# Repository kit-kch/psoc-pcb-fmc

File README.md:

# PSoC FMC Extension PCB

This repository contains schematic, layout and BOM for the PSoC FMC extension PCB.
The PCB provides all peripherals that are used to realize the [PSoC Audio Player](https://kch.dev/psoc).
It is primarily meant to be used with the Zedboard for FPGA prototyping, but it can also serve as a test board for the PSoC ASIC.

The following features are provided by the PCB:
* 98.304 MHz oscillator ([XLH53V098.304000X](doc/REN_XL_Crystal_Oscillators_Datasheet_DST_20220302-1954959-1.pdf)) for SoC clock
* 64 MBit QSPI Flash ([W25Q64JVSSIM](doc/w25q64jv_dtr_revj_03272018_plus-1489809.pdf))
* USB/UART bridge ([CP2102N](doc/cp2102n_datasheet-1634912.pdf))
* 3 LEDs
* 2 [push buttons](doc/EVPBF.pdf)
* [5-way digital joystick](doc/SKRHAAE010.pdf)
* 128x32 [OLED display](https://www.waveshare.com/0.91inch-oled-module.htm) (I2C)
* I2S DAC with output filter networks ([CS4344-CZZR](doc/CS4344-45-48_F2.pdf))
* [3.5mm audio jack](doc/sj_352x_smt-1779397.pdf) for I2S DAC
* [3.5mm audio jack](doc/sj_352x_smt-1779397.pdf) directly connected to FMC
* [MicroSD card connector](doc/MOLEX_472192001_sd.pdf) (1-bit data line only)
* Power switch network: Power PCB from FMC 12V, power connector or UART usb connector
* 5V power regulator ([AP62300WU](doc/AP62300_AP62301_AP62300T.pdf))
* 3.3V power regulator (AMS1117-3.3)
* 1.8V power regulator (LM1117MPX-ADJ)
* Power indicator LEDs
* [USB-C connector](doc/usb4110.pdf) for UART
* [USB-C connector](doc/usb4110.pdf) for power
* [FMC LPC connector](doc/asp-134604-01-mkt-1546032.pdf) to connect to FPGA or ASIC
* 2 [40-pin pin headers](doc/SBH11-NBPC.pdf) for debugging of any signal
* Connector for future extensions (based on KiCAD RFM69HW footprint)
* Arduino-like connector for future extensions

For more details, see the [schematic](psoc.pdf):

## Ordering the PCBs

PCBs were ordered from [aisler.net](https://aisler.net) using the [fab.zip](fab.zip) file.
Make sure to use a stencil with 150µm thickness for proper FMC connector soldering.

## More Information and Documentation

* Project Website and Documentation: [kch.dev/psoc](https://kch.dev/psoc)
* Project Schematic: [psoc.pdf](psoc.pdf)

Additional documentation:
* [FMC Documentation](https://fmchub.github.io/appendix/VITA57_FMC_HPC_LPC_SIGNALS_AND_PINOUT.html)
* [USB-C Termination](https://community.cypress.com/t5/Knowledge-Base-Articles/Termination-Resistors-Required-for-the-USB-Type-C-Connector/ta-p/253544)
* [Audio TRS Standard](https://components101.com/connectors/35mm-audio-jack)

## Note and Limitations

### JTAG

* The board unfortunately does not provide convenient access to JTAG pins, although the debug header can be used.
  As a workaround, [psoc-pcb-jtag](https://github.com/kit-kch/psoc-pcb-jtag) can be connected to the USB header.

### Powering the IHP ASIC

The [IHP SG13G2 ASIC](https://github.com/IHP-GmbH/TO_Sep2025/pull/4) requires an 1.2V source instead of the 1.8V on this board.
Although the regulator on the board is adjustable, it can't go down to 1.2V.

As a simple solution, some parts can be replaced to provide 1.2V output:
* `U7` with `TLV76112DCYR` 1A 1.2V regulator
* `R51` with 0 Ohm (short)
* Remove `R50`
* Remove `C26`

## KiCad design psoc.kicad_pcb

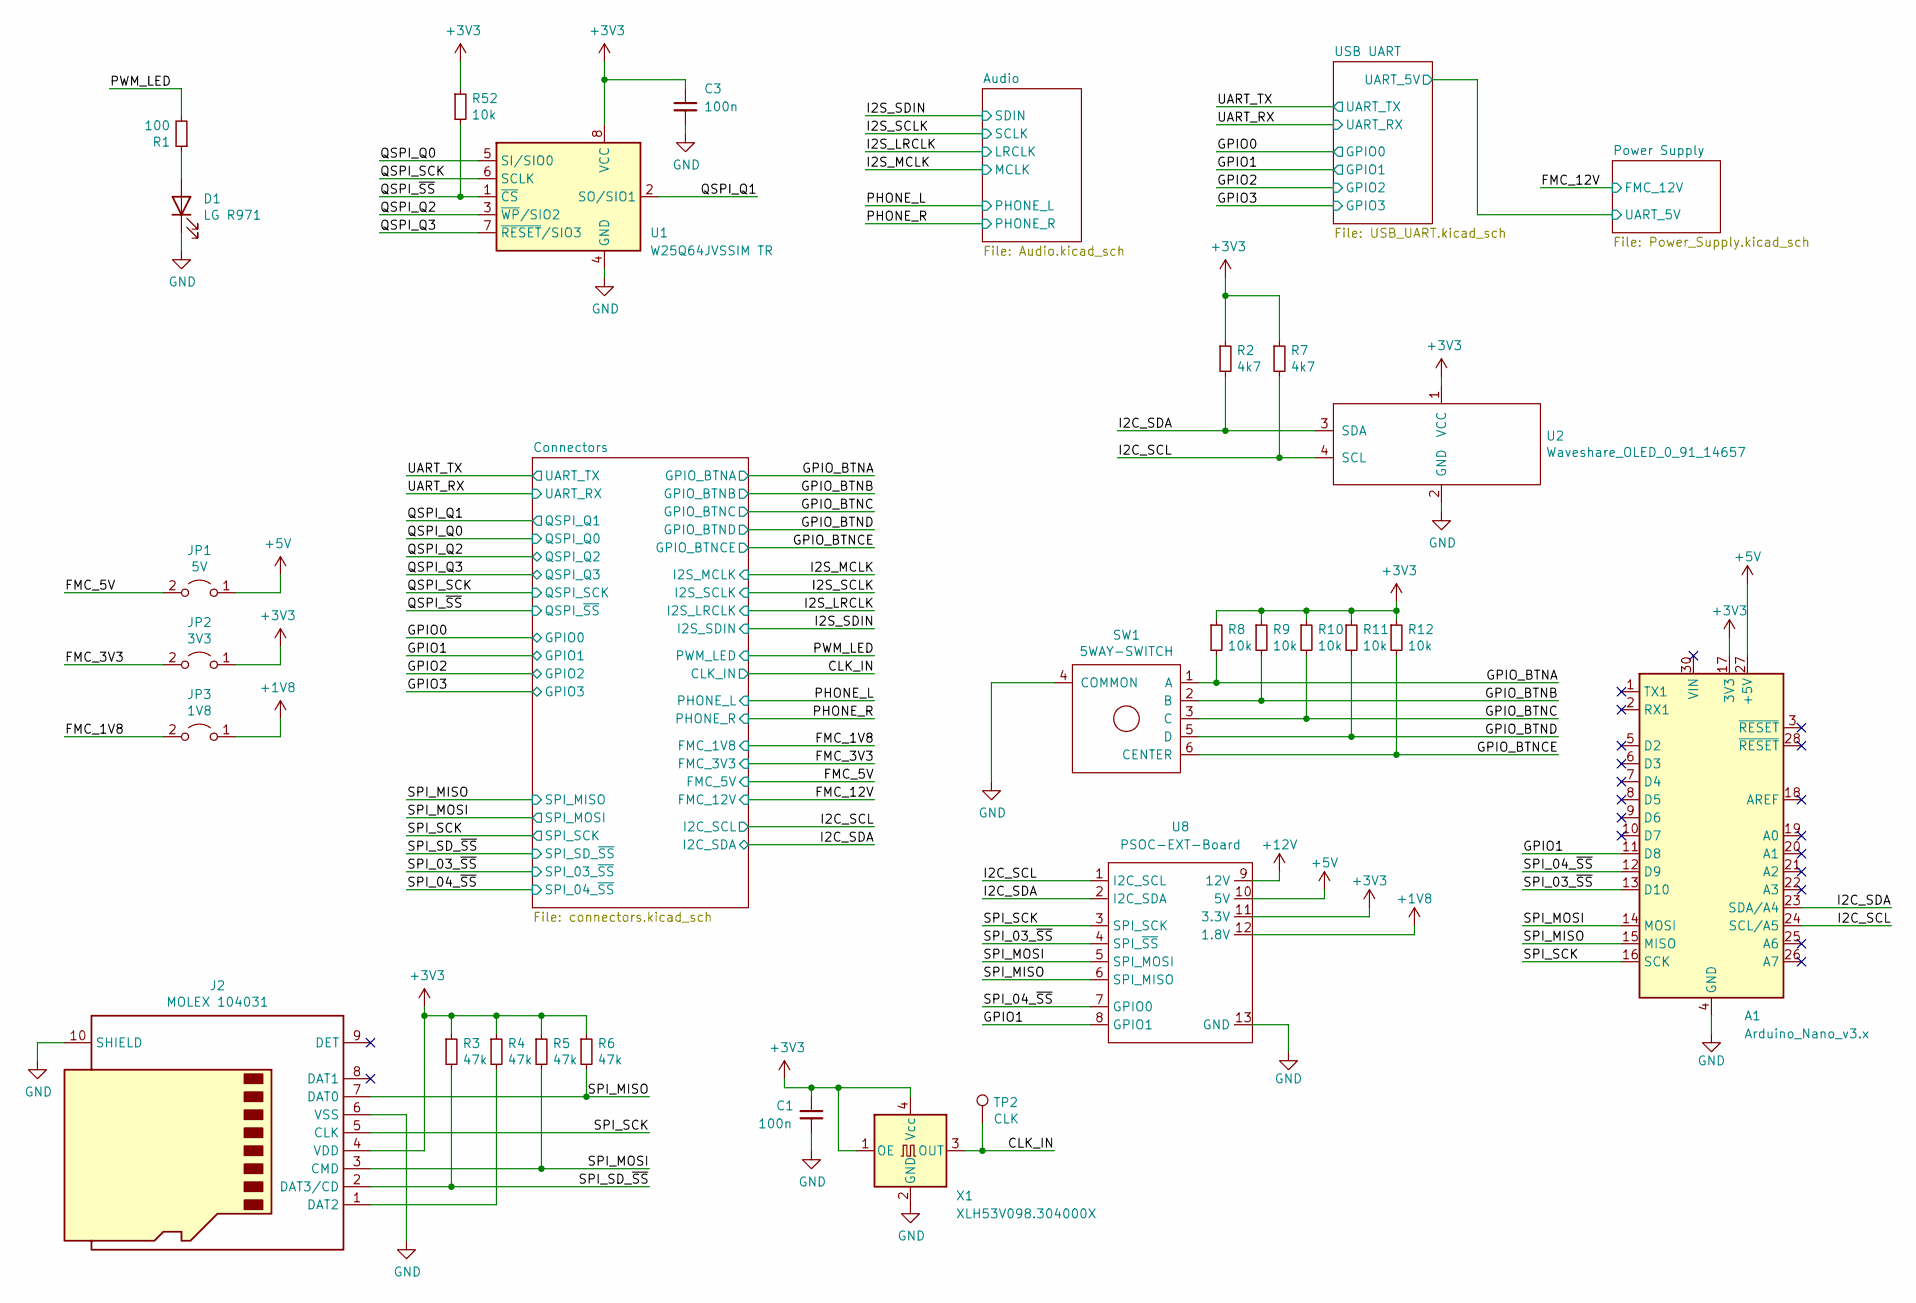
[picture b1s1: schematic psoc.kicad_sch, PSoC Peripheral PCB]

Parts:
A1: Arduino_Nano_v3.x; Arduino_Nano
C1, C3: 100n; C_0805_2012Metric; MPN 100nF 0805
D1: LG R971; LED_0805_2012Metric; MPN LG R971-KN-1
J2: MOLEX 104031; microSD_HC_Molex_104031-0811; MPN 1040310811
JP1: 5V; PinHeader_1x02_P2.54mm_Vertical; MPN 2302-6111TG
JP2: 3V3; PinHeader_1x02_P2.54mm_Vertical; MPN 2302-6111TG
JP3: 1V8; PinHeader_1x02_P2.54mm_Vertical; MPN 2302-6111TG
R1: 100; R_0805_2012Metric; MPN 0805 100
R2, R7: 4k7; R_0805_2012Metric; MPN 4k7 0805
R3, R4, R5, R6: 47k; R_0805_2012Metric; MPN 47k 0805
R8, R9, R10, R11, R12, R52: 10k; R_0805_2012Metric; MPN 10k 0805
SW1: 5WAY-SWITCH; SKRHAAE010; MPN SKRHAAE010
TP2: CLK; TestPoint_Pad_1.0x1.0mm
U1: W25Q64JVSSIM TR; SOIC-8_5.3x5.3mm_P1.27mm; MPN W25Q64JVSSIM TR
U2: Waveshare_OLED_0_91_14657; Waveshare_OLED_091
U8: PSOC-EXT-Board; PSOC_EXT_BOARD
X1: XLH53V098.304000X; Oscillator_SMD_Renesas_LGA-6_5x3.2mm_P1.25mm; MPN XLH53V098.304000X

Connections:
+1V8: JP3.1 (A), U8.12 (1.8V); also elsewhere on the board
+3V3: A1.17 (3V3), C1.1, C3.1, J2.4 (VDD), JP2.1 (A), R2.1, R3.1, R4.1, R5.1, R6.1, R7.1, R8.1, R9.1, R10.1, R11.1, R12.1, R52.1, U1.8 (VCC), U2.1 (VCC), U8.11 (3.3V), X1.1 (OE), X1.4 (Vcc); also elsewhere on the board
+5V: A1.27 (+5V), JP1.1 (A), U8.10 (5V); also elsewhere on the board
+12V: U8.9 (12V); also elsewhere on the board
/CLK_IN: TP2.1, X1.3 (OUT); also elsewhere on the board
/FMC_1V8: JP3.2 (B); also elsewhere on the board
/FMC_3V3: JP2.2 (B); also elsewhere on the board
/FMC_5V: JP1.2 (B); also elsewhere on the board
/GPIO1: A1.11 (D8), U8.8 (GPIO1); also elsewhere on the board
/GPIO_BTNA: R8.2, SW1.1 (A); also elsewhere on the board
/GPIO_BTNB: R9.2, SW1.2 (B); also elsewhere on the board
/GPIO_BTNC: R10.2, SW1.3 (C); also elsewhere on the board
/GPIO_BTNCE: R12.2, SW1.6 (CENTER); also elsewhere on the board
/GPIO_BTND: R11.2, SW1.5 (D); also elsewhere on the board
/I2C_SCL: A1.24 (SCL/A5), R7.2, U2.4 (SCL), U8.1 (I2C_SCL); also elsewhere on the board
/I2C_SDA: A1.23 (SDA/A4), R2.2, U2.3 (SDA), U8.2 (I2C_SDA); also elsewhere on the board
/PWM_LED: R1.2; also elsewhere on the board
/QSPI_Q0: U1.5 (SI/SIO0); also elsewhere on the board
/QSPI_Q1: U1.2 (SO/SIO1); also elsewhere on the board
/QSPI_Q2: U1.3 (~WP/SIO2); also elsewhere on the board
/QSPI_Q3: U1.7 (~RESET/SIO3); also elsewhere on the board
/QSPI_SCK: U1.6 (SCLK); also elsewhere on the board
/QSPI_~SS: R52.2, U1.1 (~CS); also elsewhere on the board
/SPI_03_~SS: A1.13 (D10), U8.4 (SPI_~SS); also elsewhere on the board
/SPI_04_~SS: A1.12 (D9), U8.7 (GPIO0); also elsewhere on the board
/SPI_MISO: A1.15 (MISO), J2.7 (DAT0), R6.2, U8.6 (SPI_MISO); also elsewhere on the board
/SPI_MOSI: A1.14 (MOSI), J2.3 (CMD), R5.2, U8.5 (SPI_MOSI); also elsewhere on the board
/SPI_SCK: A1.16 (SCK), J2.5 (CLK), U8.3 (SPI_SCK); also elsewhere on the board
/SPI_SD_~SS: J2.2 (DAT3/CD), R3.2; also elsewhere on the board
GND: A1.4 (GND), A1.29 (GND), C1.2, C3.2, D1.1 (K), J2.6 (VSS), J2.10 (SHIELD), J2.11 (SHIELD), SW1.4 (COMMON), U1.4 (GND), U2.2 (GND), U8.13 (GND), X1.2 (GND); also elsewhere on the board
unnamed: D1.2 (A), R1.1
unnamed: J2.1 (DAT2), R4.2

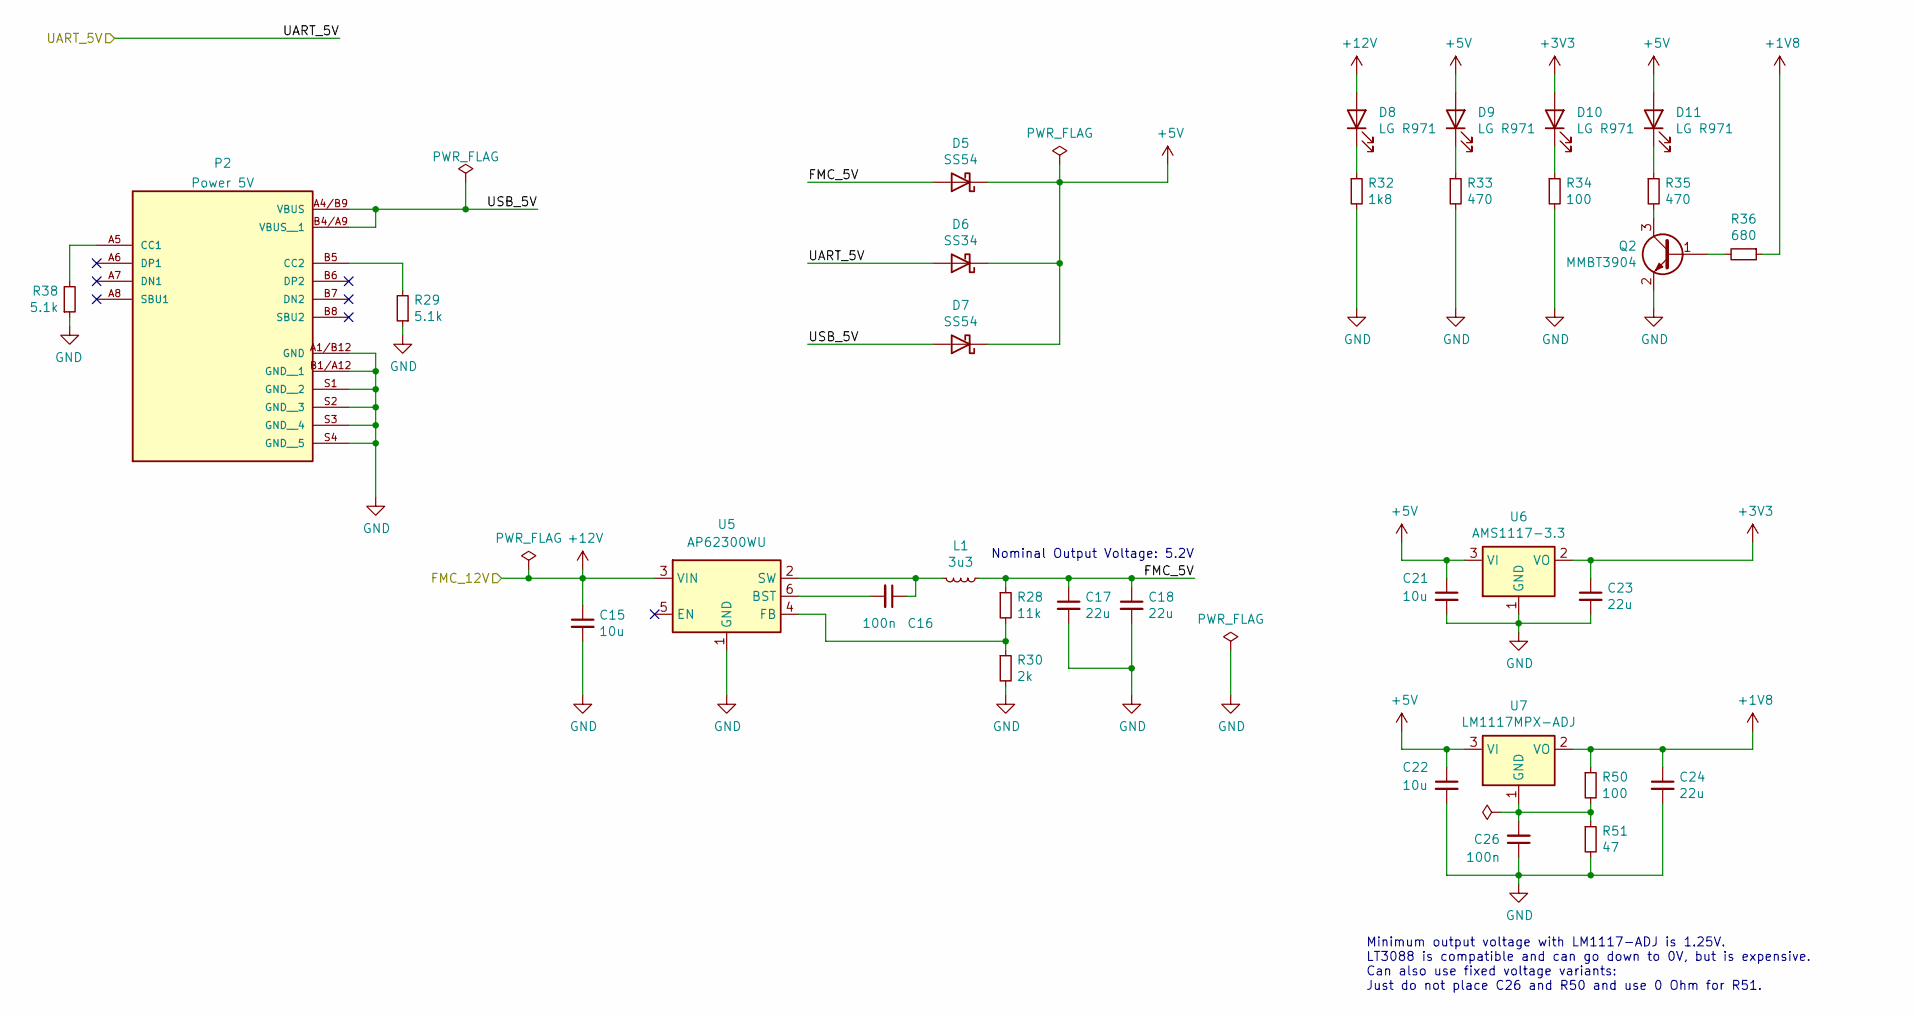
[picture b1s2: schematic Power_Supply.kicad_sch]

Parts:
C15, C21, C22: 10u; C_0805_2012Metric; MPN 10uF 0805 25V
C16, C26: 100n; C_0805_2012Metric; MPN 100nF 0805
C17, C18, C23, C24: 22u; C_0805_2012Metric; MPN 22uF 0805
D5, D7: SS54; D_SMA; MPN SS54
D6: SS34; D_SMA; MPN SS34
D8, D9, D10, D11: LG R971; LED_0805_2012Metric; MPN LG R971-KN-1
L1: 3u3; L_Taiyo-Yuden_NR-50xx; MPN NRS5040T3R3NMGJ
P2: Power 5V; GCT_USB4110-GF-A_REVB; MPN USB4110-GF-A
Q2: MMBT3904; SOT-23; MPN MMBT3904Q-7-F
R28: 11k; R_0805_2012Metric; MPN 11k 0805
R29, R38: 5.1k; R_0805_2012Metric; MPN 5k1 0805
R30: 2k; R_0805_2012Metric; MPN 2k 0805
R32: 1k8; R_0805_2012Metric; MPN 1k8 0805
R33, R35: 470; R_0805_2012Metric; MPN 0805 470
R34: 100; R_0805_2012Metric; MPN 0805 100
R36: 680; R_0805_2012Metric; MPN 0805 680
R50: 100; R_0805_2012Metric; MPN 100 0805
R51: 47; R_0805_2012Metric; MPN 47 0805
U5: AP62300WU; TSOT-23-6; MPN AP62301WU-7
U6: AMS1117-3.3; TO-252-3_TabPin2; MPN AZ1117IH-3.3TRG1
U7: LM1117MPX-ADJ; TO-252-3_TabPin2; MPN LM1117MPX-ADJNOPB

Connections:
+1V8: C24.1, R36.1, R50.1, U7.2 (VO); also elsewhere on the board
+3V3: C23.1, D10.2 (A), U6.2 (VO); also elsewhere on the board
+5V: C21.1, C22.1, D5.1 (K), D6.1 (K), D7.1 (K), D9.2 (A), D11.2 (A), U6.3 (VI), U7.3 (VI); also elsewhere on the board
+12V: C15.1, D8.2 (A), U5.3 (VIN); also elsewhere on the board
/Power Supply/FMC_5V: C17.1, C18.1, D5.2 (A), L1.1, R28.1
/Power Supply/UART_5V: D6.2 (A); also elsewhere on the board
/Power Supply/USB_5V: D7.2 (A), P2.A4/B9 (VBUS), P2.B4/A9 (VBUS__1)
GND: C15.2, C17.2, C18.2, C21.2, C22.2, C23.2, C24.2, C26.1, P2.A1/B12 (GND), P2.B1/A12 (GND__1), P2.S1 (GND__2), P2.S2 (GND__3), P2.S3 (GND__4), P2.S4 (GND__5), Q2.2 (E), R29.1, R30.2, R32.2, R33.2, R34.2, R38.1, R51.2, U5.1 (GND), U6.1 (GND); also elsewhere on the board
unnamed: C16.1, L1.2, U5.2 (SW)
unnamed: C16.2, U5.6 (BST)
unnamed: C26.2, R50.2, R51.1, U7.1 (GND)
unnamed: D8.1 (K), R32.1
unnamed: D9.1 (K), R33.1
unnamed: D10.1 (K), R34.1
unnamed: D11.1 (K), R35.1
unnamed: P2.A5 (CC1), R38.2
unnamed: P2.B5 (CC2), R29.2
unnamed: Q2.1 (B), R36.2
unnamed: Q2.3 (C), R35.2
unnamed: R28.2, R30.1, U5.4 (FB)

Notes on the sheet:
Minimum output voltage with LM1117-ADJ is 1.25V. LT3088 is compatible and can go down to 0V, but is expensive. Can also use fixed voltage variants: Just do not place C26 and R50 and use 0 Ohm for R51.
Nominal Output Voltage: 5.2V

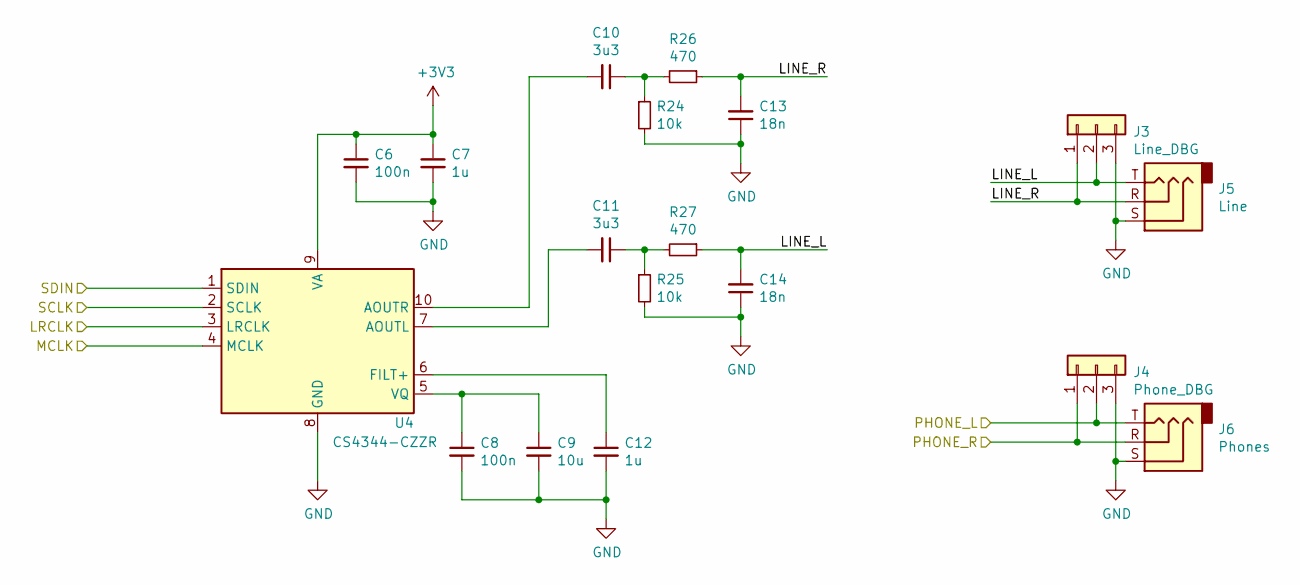
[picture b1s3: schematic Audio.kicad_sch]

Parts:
C6, C8: 100n; C_0805_2012Metric; MPN 100nF 0805
C7, C12: 1u; C_0805_2012Metric; MPN 1uF 0805
C9: 10u; C_0805_2012Metric; MPN 10uF 0805 25V
C10, C11: 3u3; C_0805_2012Metric; MPN 3.3uF 0805
C13, C14: 18n; C_0805_2012Metric; MPN 18nF 0805
J3: Line_DBG; PinHeader_1x03_P2.54mm_Vertical; MPN 2303-6111TG
J4: Phone_DBG; PinHeader_1x03_P2.54mm_Vertical; MPN 2303-6111TG
J5: Line; Jack_3.5mm_CUI_SJ-3523-SMT_Horizontal; MPN SJ-3523-SMT-TR
J6: Phones; Jack_3.5mm_CUI_SJ-3523-SMT_Horizontal; MPN SJ-3523-SMT-TR
R24, R25: 10k; R_0805_2012Metric; MPN 10k 0805
R26, R27: 470; R_0805_2012Metric; MPN 0805 470
U4: CS4344-CZZR; TSSOP-10_3x3mm_P0.5mm; MPN CS4344-CZZR

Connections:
+3V3: C6.1, C7.1, U4.9 (VA); also elsewhere on the board
/Audio/LINE_L: C14.2, J3.2, J5.T, R27.1
/Audio/LINE_R: C13.2, J3.1, J5.R, R26.1
/I2S_LRCLK: U4.3 (LRCLK); also elsewhere on the board
/I2S_MCLK: U4.4 (MCLK); also elsewhere on the board
/I2S_SCLK: U4.2 (SCLK); also elsewhere on the board
/I2S_SDIN: U4.1 (SDIN); also elsewhere on the board
/PHONE_L: J4.2, J6.T; also elsewhere on the board
/PHONE_R: J4.1, J6.R; also elsewhere on the board
GND: C6.2, C7.2, C8.2, C9.2, C12.2, C13.1, C14.1, J3.3, J4.3, J5.S, J6.S, R24.2, R25.2, U4.8 (GND); also elsewhere on the board
unnamed: C8.1, C9.1, U4.5 (VQ)
unnamed: C10.1, R24.1, R26.2
unnamed: C10.2, U4.10 (AOUTR)
unnamed: C11.1, R25.1, R27.2
unnamed: C11.2, U4.7 (AOUTL)
unnamed: C12.1, U4.6 (FILT+)

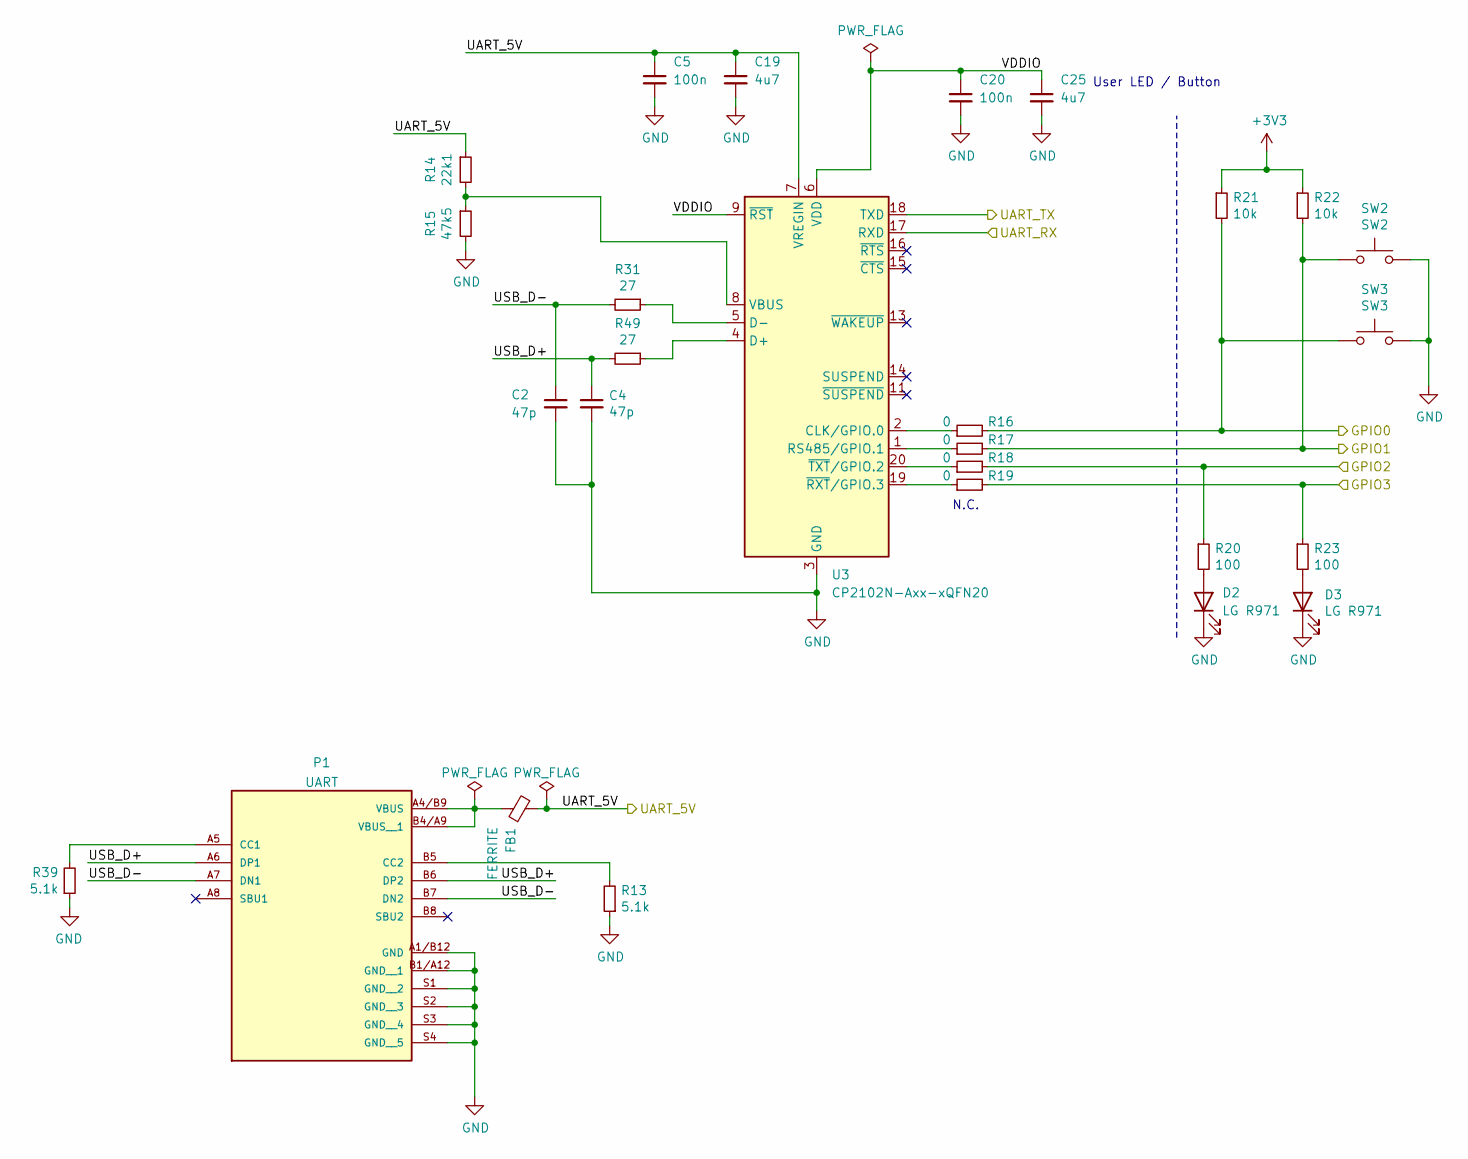
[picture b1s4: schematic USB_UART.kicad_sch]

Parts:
C2, C4: 47p; C_0805_2012Metric; MPN 47pF 0805
C5, C20: 100n; C_0805_2012Metric; MPN 100nF 0805
C19, C25: 4u7; C_0805_2012Metric; MPN 4.7uF 0805
D2, D3: LG R971; LED_0805_2012Metric; MPN LG R971-KN-1
FB1: FERRITE; L_0805_2012Metric; MPN ACML-0805-301-T
P1: UART; GCT_USB4110-GF-A_REVB; MPN USB4110-GF-A
R13, R39: 5.1k; R_0805_2012Metric; MPN 5k1 0805
R14: 22k1; R_0805_2012Metric; MPN 22k1 0805
R15: 47k5; R_0805_2012Metric; MPN 0805 47.5k
R16, R17, R18, R19: 0; R_0805_2012Metric; MPN 0805 0.0
R20, R23: 100; R_0805_2012Metric; MPN 0805 100
R21, R22: 10k; R_0805_2012Metric; MPN 10k 0805
R31, R49: 27; R_0805_2012Metric; MPN 0805 27
SW2: SW2; SW_SPST_EVPBF; MPN EVP-BF6C1A000
SW3: SW3; SW_SPST_EVPBF; MPN EVP-BF6C1A000
U3: CP2102N-Axx-xQFN20; SiliconLabs_QFN-20-1EP_3x3mm_P0.5mm_EP1.8x1.8mm; MPN CP2102N-A02-GQFN20

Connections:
+3V3: R21.1, R22.1; also elsewhere on the board
/GPIO0: R16.2, R21.2, SW3.1; also elsewhere on the board
/GPIO1: R17.2, R22.2, SW2.1; also elsewhere on the board
/GPIO2: R18.2, R20.1; also elsewhere on the board
/GPIO3: R19.2, R23.1; also elsewhere on the board
/Power Supply/UART_5V: C5.1, C19.1, FB1.2, R14.1, U3.7 (VREGIN); also elsewhere on the board
/UART_RX: U3.17 (RXD); also elsewhere on the board
/UART_TX: U3.18 (TXD); also elsewhere on the board
/USB UART/USB_D+: C4.1, P1.A6 (DP1), P1.B6 (DP2), R49.2
/USB UART/USB_D-: C2.1, P1.A7 (DN1), P1.B7 (DN2), R31.2
/USB UART/VDDIO: C20.1, C25.1, U3.6 (VDD), U3.9 (~RST)
GND: C2.2, C4.2, C5.2, C19.2, C20.2, C25.2, D2.1 (K), D3.1 (K), P1.A1/B12 (GND), P1.B1/A12 (GND__1), P1.S1 (GND__2), P1.S2 (GND__3), P1.S3 (GND__4), P1.S4 (GND__5), R13.1, R15.2, R39.1, SW2.2, SW3.2, U3.3 (GND), U3.12 (GND), U3.21 (GND); also elsewhere on the board
unnamed: D2.2 (A), R20.2
unnamed: D3.2 (A), R23.2
unnamed: FB1.1, P1.A4/B9 (VBUS), P1.B4/A9 (VBUS__1)
unnamed: P1.A5 (CC1), R39.2
unnamed: P1.B5 (CC2), R13.2
unnamed: R14.2, R15.1, U3.8 (VBUS)
unnamed: R16.1, U3.2 (CLK/GPIO.0)
unnamed: R17.1, U3.1 (RS485/GPIO.1)
unnamed: R18.1, U3.20 (~TXT/GPIO.2)
unnamed: R19.1, U3.19 (~RXT/GPIO.3)
unnamed: R31.1, U3.5 (D-)
unnamed: R49.1, U3.4 (D+)

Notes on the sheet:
User LED / Button
N.C.

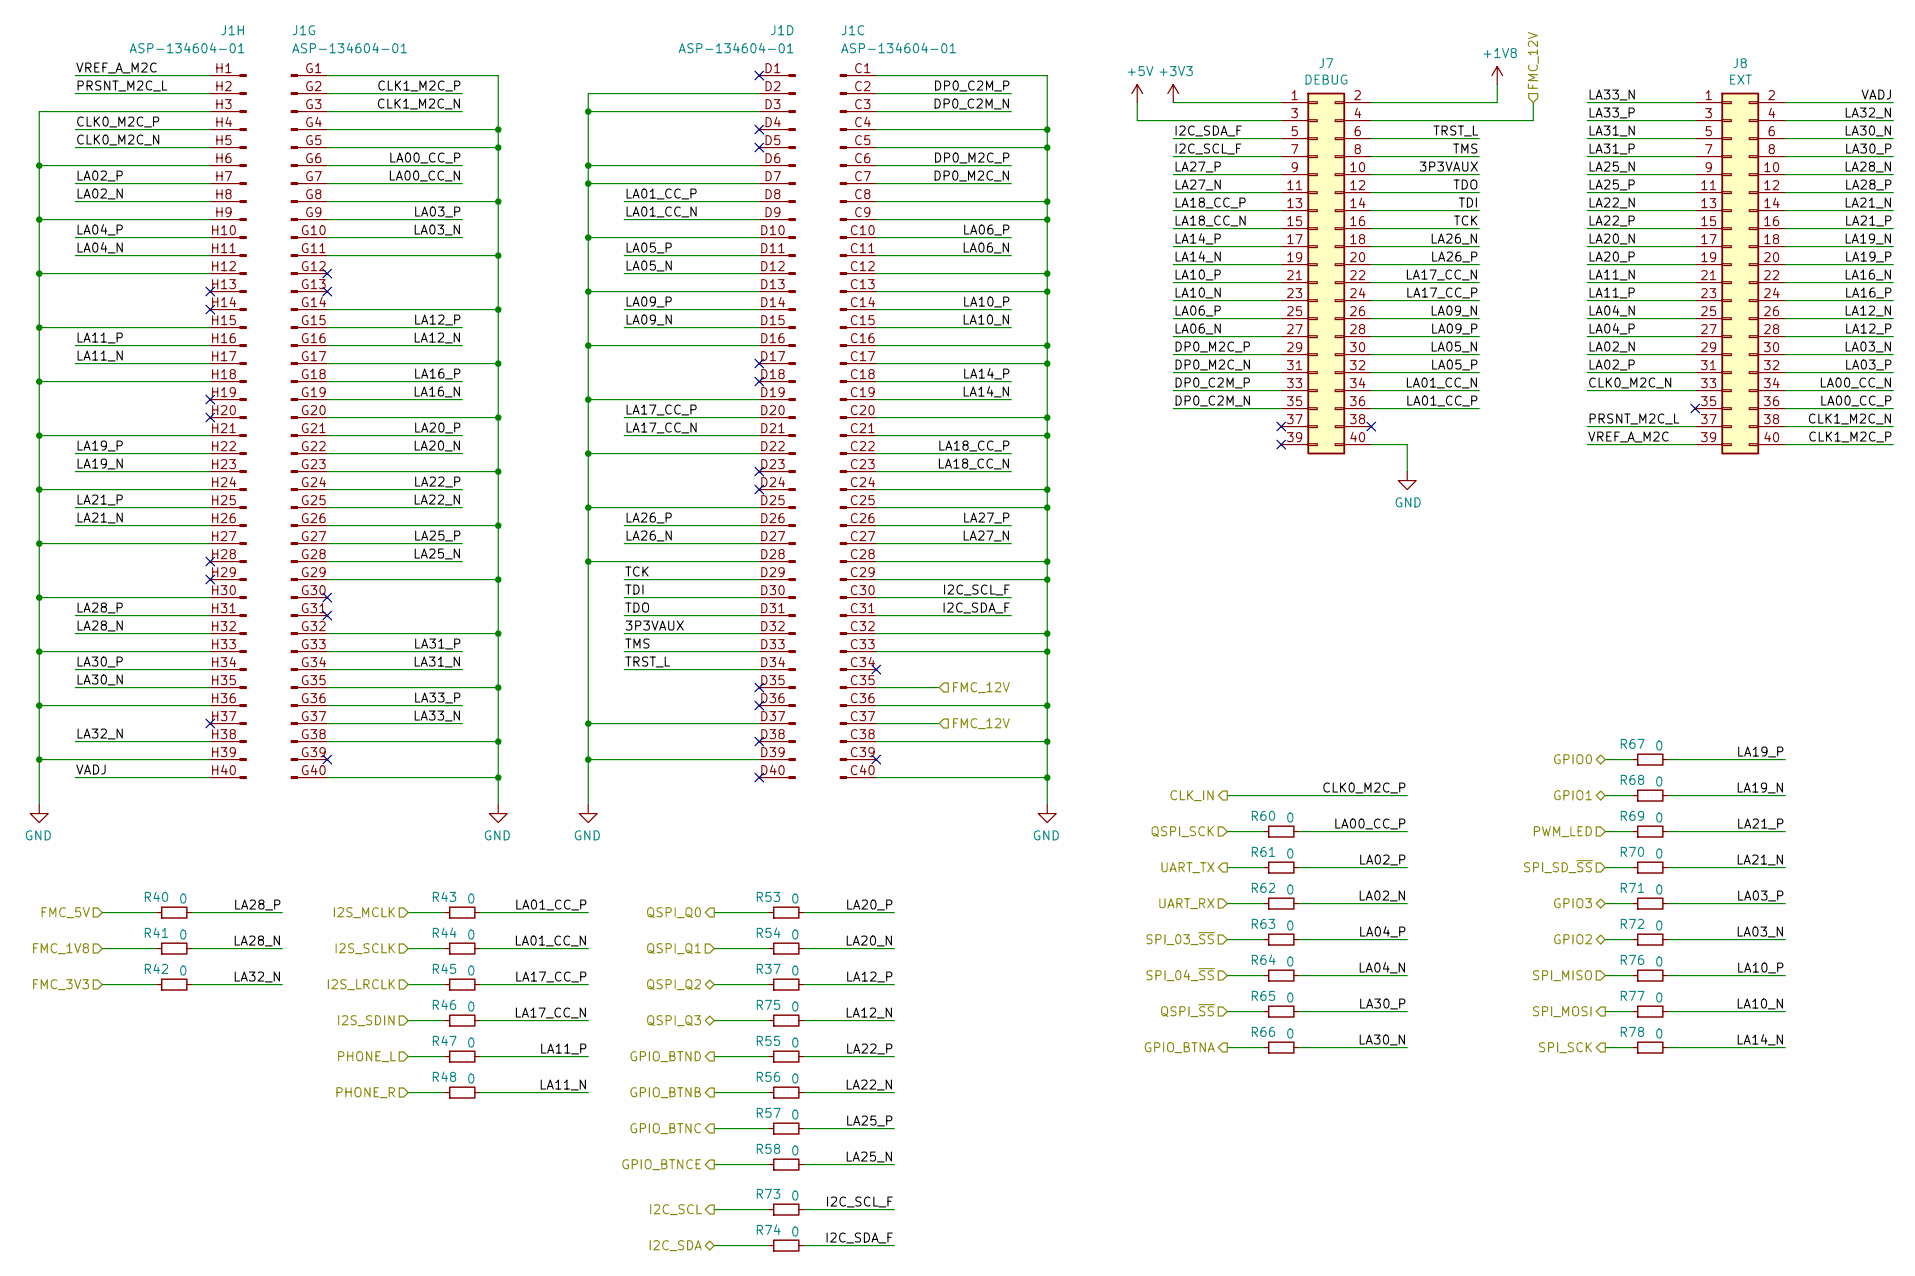
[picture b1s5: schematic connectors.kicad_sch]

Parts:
J1: ASP-134604-01; Samtec_FMC_ASP-134604-01_4x40_Vertical; MPN ASP-134604-01
J7: DEBUG; Pin-Header_ SBH11-NBPC-D20-SM-BK; MPN SBH11-NBPC-D20-SM-BK
J8: EXT; Pin-Header_ SBH11-NBPC-D20-SM-BK; MPN SBH11-NBPC-D20-SM-BK
R37, R40, R41, R42, R43, R44, R45, R46, R47, R48, R53, R54, R55, R56, R57, R58, R60, R61, R62, R63, R64, R65, R66, R67, R68, R69, R70, R71, R72, R73, R74, R75, R76, R77, R78: 0; R_0805_2012Metric; MPN 0805 0.0

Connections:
+1V8: J7.2; also elsewhere on the board
+3V3: J7.1; also elsewhere on the board
+5V: J7.3; also elsewhere on the board
+12V: J1.C35 (Pin_35), J1.C37 (Pin_37), J7.4; also elsewhere on the board
/CLK_IN: J1.H4 (Pin_4); also elsewhere on the board
/Connectors/3P3VAUX: J1.D32 (Pin_32), J7.10
/Connectors/CLK0_M2C_N: J1.H5 (Pin_5), J8.33
/Connectors/CLK1_M2C_N: J1.G3 (Pin_3), J8.38
/Connectors/CLK1_M2C_P: J1.G2 (Pin_2), J8.40
/Connectors/DP0_C2M_N: J1.C3 (Pin_3), J7.35
/Connectors/DP0_C2M_P: J1.C2 (Pin_2), J7.33
/Connectors/DP0_M2C_N: J1.C7 (Pin_7), J7.31
/Connectors/DP0_M2C_P: J1.C6 (Pin_6), J7.29
/Connectors/I2C_SCL_F: J1.C30 (Pin_30), J7.7, R73.2
/Connectors/I2C_SDA_F: J1.C31 (Pin_31), J7.5, R74.2
/Connectors/LA00_CC_N: J1.G7 (Pin_7), J8.34
/Connectors/LA00_CC_P: J1.G6 (Pin_6), J8.36, R60.2
/Connectors/LA01_CC_N: J1.D9 (Pin_9), J7.34, R44.2
/Connectors/LA01_CC_P: J1.D8 (Pin_8), J7.36, R43.2
/Connectors/LA02_N: J1.H8 (Pin_8), J8.29, R62.2
/Connectors/LA02_P: J1.H7 (Pin_7), J8.31, R61.2
/Connectors/LA03_N: J1.G10 (Pin_10), J8.30, R72.2
/Connectors/LA03_P: J1.G9 (Pin_9), J8.32, R71.2
/Connectors/LA04_N: J1.H11 (Pin_11), J8.25, R64.2
/Connectors/LA04_P: J1.H10 (Pin_10), J8.27, R63.2
/Connectors/LA05_N: J1.D12 (Pin_12), J7.30
/Connectors/LA05_P: J1.D11 (Pin_11), J7.32
/Connectors/LA06_N: J1.C11 (Pin_11), J7.27
/Connectors/LA06_P: J1.C10 (Pin_10), J7.25
/Connectors/LA09_N: J1.D15 (Pin_15), J7.26
/Connectors/LA09_P: J1.D14 (Pin_14), J7.28
/Connectors/LA10_N: J1.C15 (Pin_15), J7.23, R77.2
/Connectors/LA10_P: J1.C14 (Pin_14), J7.21, R76.2
/Connectors/LA11_N: J1.H17 (Pin_17), J8.21, R48.2
/Connectors/LA11_P: J1.H16 (Pin_16), J8.23, R47.2
/Connectors/LA12_N: J1.G16 (Pin_16), J8.26, R75.2
/Connectors/LA12_P: J1.G15 (Pin_15), J8.28, R37.2
/Connectors/LA14_N: J1.C19 (Pin_19), J7.19, R78.2
/Connectors/LA14_P: J1.C18 (Pin_18), J7.17
/Connectors/LA16_N: J1.G19 (Pin_19), J8.22
/Connectors/LA16_P: J1.G18 (Pin_18), J8.24
/Connectors/LA17_CC_N: J1.D21 (Pin_21), J7.22, R46.2
/Connectors/LA17_CC_P: J1.D20 (Pin_20), J7.24, R45.2
/Connectors/LA18_CC_N: J1.C23 (Pin_23), J7.15
/Connectors/LA18_CC_P: J1.C22 (Pin_22), J7.13
/Connectors/LA19_N: J1.H23 (Pin_23), J8.18, R68.2
/Connectors/LA19_P: J1.H22 (Pin_22), J8.20, R67.2
/Connectors/LA20_N: J1.G22 (Pin_22), J8.17, R54.2
/Connectors/LA20_P: J1.G21 (Pin_21), J8.19, R53.2
/Connectors/LA21_N: J1.H26 (Pin_26), J8.14, R70.2
/Connectors/LA21_P: J1.H25 (Pin_25), J8.16, R69.2
/Connectors/LA22_N: J1.G25 (Pin_25), J8.13, R56.2
/Connectors/LA22_P: J1.G24 (Pin_24), J8.15, R55.2
/Connectors/LA25_N: J1.G28 (Pin_28), J8.9, R58.2
/Connectors/LA25_P: J1.G27 (Pin_27), J8.11, R57.2
/Connectors/LA26_N: J1.D27 (Pin_27), J7.18
/Connectors/LA26_P: J1.D26 (Pin_26), J7.20
/Connectors/LA27_N: J1.C27 (Pin_27), J7.11
/Connectors/LA27_P: J1.C26 (Pin_26), J7.9
/Connectors/LA28_N: J1.H32 (Pin_32), J8.10, R41.2
/Connectors/LA28_P: J1.H31 (Pin_31), J8.12, R40.2
/Connectors/LA30_N: J1.H35 (Pin_35), J8.6, R66.2
/Connectors/LA30_P: J1.H34 (Pin_34), J8.8, R65.2
/Connectors/LA31_N: J1.G34 (Pin_34), J8.5
/Connectors/LA31_P: J1.G33 (Pin_33), J8.7
/Connectors/LA32_N: J1.H38 (Pin_38), J8.4, R42.2
/Connectors/LA33_N: J1.G37 (Pin_37), J8.1
/Connectors/LA33_P: J1.G36 (Pin_36), J8.3
/Connectors/PRSNT_M2C_L: J1.H2 (Pin_2), J8.37
/Connectors/TCK: J1.D29 (Pin_29), J7.16
/Connectors/TDI: J1.D30 (Pin_30), J7.14
/Connectors/TDO: J1.D31 (Pin_31), J7.12
/Connectors/TMS: J1.D33 (Pin_33), J7.8
/Connectors/TRST_L: J1.D34 (Pin_34), J7.6
/Connectors/VADJ: J1.H40 (Pin_40), J8.2
/Connectors/VREF_A_M2C: J1.H1 (Pin_1), J8.39
/FMC_1V8: R41.1; also elsewhere on the board
/FMC_3V3: R42.1; also elsewhere on the board
/FMC_5V: R40.1; also elsewhere on the board
/GPIO0: R67.1; also elsewhere on the board
/GPIO1: R68.1; also elsewhere on the board
/GPIO2: R72.1; also elsewhere on the board
/GPIO3: R71.1; also elsewhere on the board
/GPIO_BTNA: R66.1; also elsewhere on the board
/GPIO_BTNB: R56.1; also elsewhere on the board
/GPIO_BTNC: R57.1; also elsewhere on the board
/GPIO_BTNCE: R58.1; also elsewhere on the board
/GPIO_BTND: R55.1; also elsewhere on the board
/I2C_SCL: R73.1; also elsewhere on the board
/I2C_SDA: R74.1; also elsewhere on the board
/I2S_LRCLK: R45.1; also elsewhere on the board
/I2S_MCLK: R43.1; also elsewhere on the board
/I2S_SCLK: R44.1; also elsewhere on the board
/I2S_SDIN: R46.1; also elsewhere on the board
/PHONE_L: R47.1; also elsewhere on the board
/PHONE_R: R48.1; also elsewhere on the board
/PWM_LED: R69.1; also elsewhere on the board
/QSPI_Q0: R53.1; also elsewhere on the board
/QSPI_Q1: R54.1; also elsewhere on the board
/QSPI_Q2: R37.1; also elsewhere on the board
/QSPI_Q3: R75.1; also elsewhere on the board
/QSPI_SCK: R60.1; also elsewhere on the board
/QSPI_~SS: R65.1; also elsewhere on the board
/SPI_03_~SS: R63.1; also elsewhere on the board
/SPI_04_~SS: R64.1; also elsewhere on the board
/SPI_MISO: R76.1; also elsewhere on the board
/SPI_MOSI: R77.1; also elsewhere on the board
/SPI_SCK: R78.1; also elsewhere on the board
/SPI_SD_~SS: R70.1; also elsewhere on the board
/UART_RX: R62.1; also elsewhere on the board
/UART_TX: R61.1; also elsewhere on the board
GND: J1.C1 (Pin_1), J1.C4 (Pin_4), J1.C5 (Pin_5), J1.C8 (Pin_8), J1.C9 (Pin_9), J1.C12 (Pin_12), J1.C13 (Pin_13), J1.C16 (Pin_16), J1.C17 (Pin_17), J1.C20 (Pin_20), J1.C21 (Pin_21), J1.C24 (Pin_24), J1.C25 (Pin_25), J1.C28 (Pin_28), J1.C29 (Pin_29), J1.C32 (Pin_32), J1.C33 (Pin_33), J1.C36 (Pin_36), J1.C38 (Pin_38), J1.C40 (Pin_40), J1.D2 (Pin_2), J1.D3 (Pin_3), J1.D6 (Pin_6), J1.D7 (Pin_7), J1.D10 (Pin_10), J1.D13 (Pin_13), J1.D16 (Pin_16), J1.D19 (Pin_19), J1.D22 (Pin_22), J1.D25 (Pin_25), J1.D28 (Pin_28), J1.D37 (Pin_37), J1.D39 (Pin_39), J1.G1 (Pin_1), J1.G4 (Pin_4), J1.G5 (Pin_5), J1.G8 (Pin_8), J1.G11 (Pin_11), J1.G14 (Pin_14), J1.G17 (Pin_17), J1.G20 (Pin_20), J1.G23 (Pin_23), J1.G26 (Pin_26), J1.G29 (Pin_29), J1.G32 (Pin_32), J1.G35 (Pin_35), J1.G38 (Pin_38), J1.G40 (Pin_40), J1.H3 (Pin_3), J1.H6 (Pin_6), J1.H9 (Pin_9), J1.H12 (Pin_12), J1.H15 (Pin_15), J1.H18 (Pin_18), J1.H21 (Pin_21), J1.H24 (Pin_24), J1.H27 (Pin_27), J1.H30 (Pin_30), J1.H33 (Pin_33), J1.H36 (Pin_36), J1.H39 (Pin_39), J7.40; also elsewhere on the board

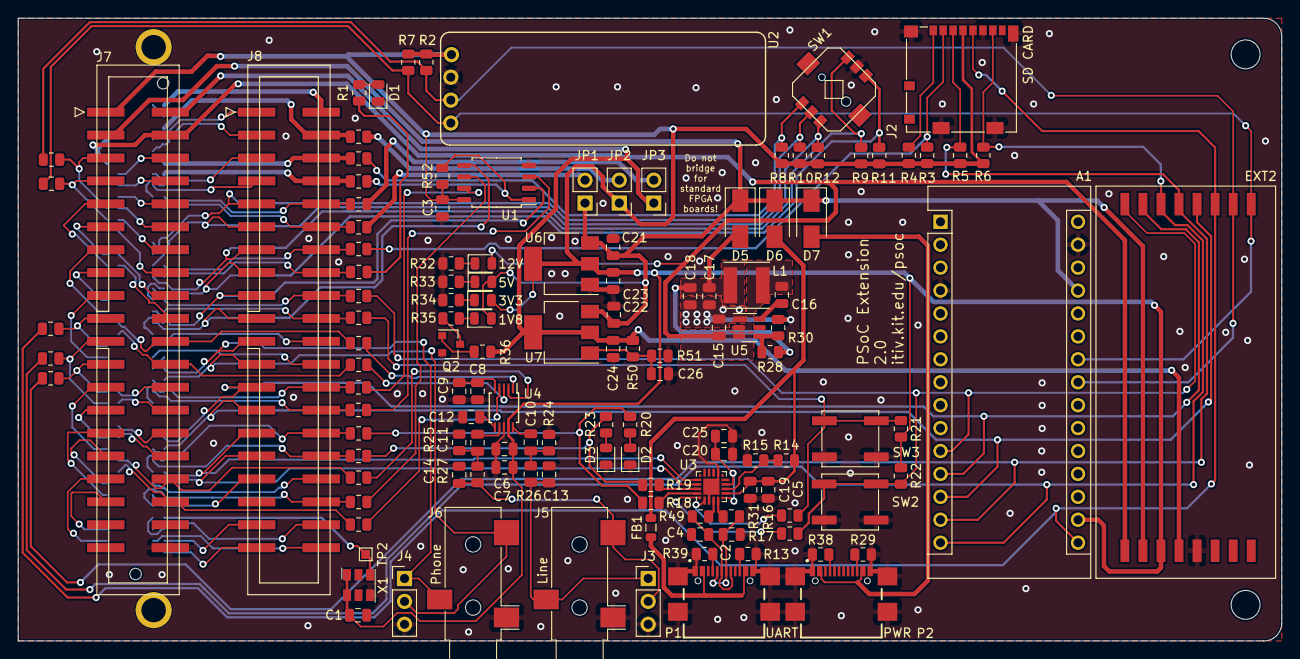
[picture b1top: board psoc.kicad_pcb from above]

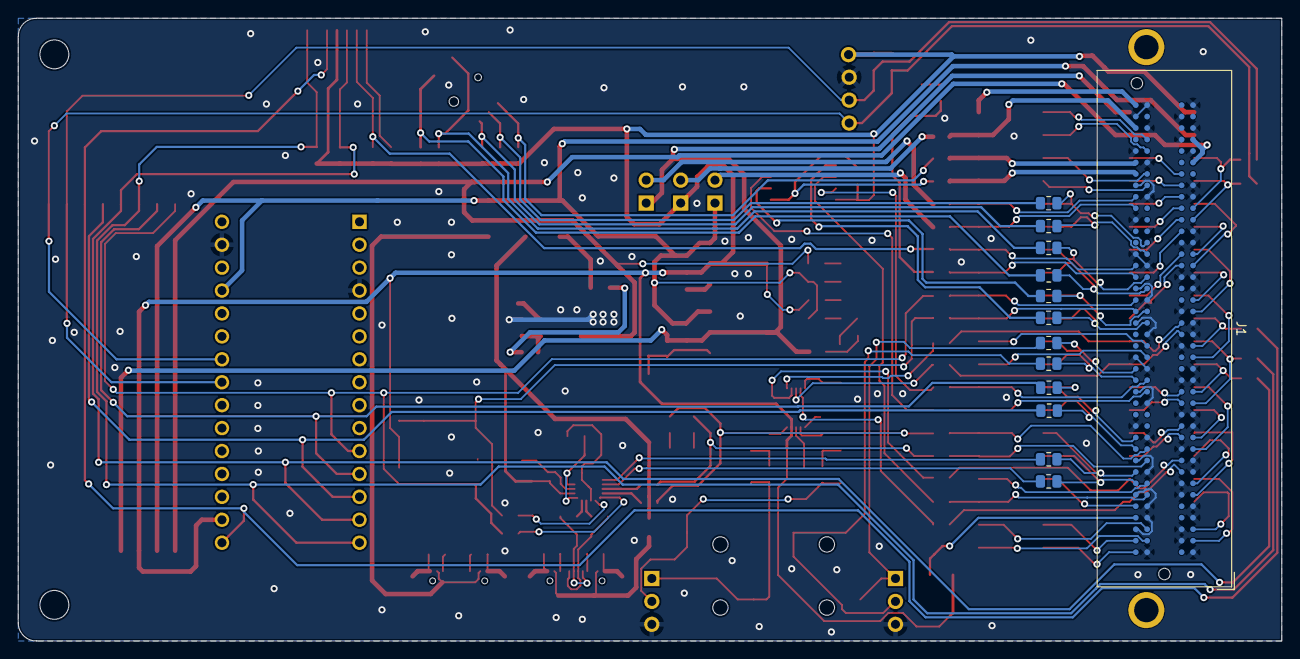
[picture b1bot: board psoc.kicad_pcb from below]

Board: 2 copper layers, 140.0 x 69.0 mm, 143 parts (13 on the bottom side), 152 nets.

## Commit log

2025-09-11 Public release
2025-09-11 Fix SD card link
2025-09-11 Fix aisler link
2025-09-11 Fix typo
2025-10-08 Use picture of board instead of incomplete render image
2025-10-08 Remove black border from foto
